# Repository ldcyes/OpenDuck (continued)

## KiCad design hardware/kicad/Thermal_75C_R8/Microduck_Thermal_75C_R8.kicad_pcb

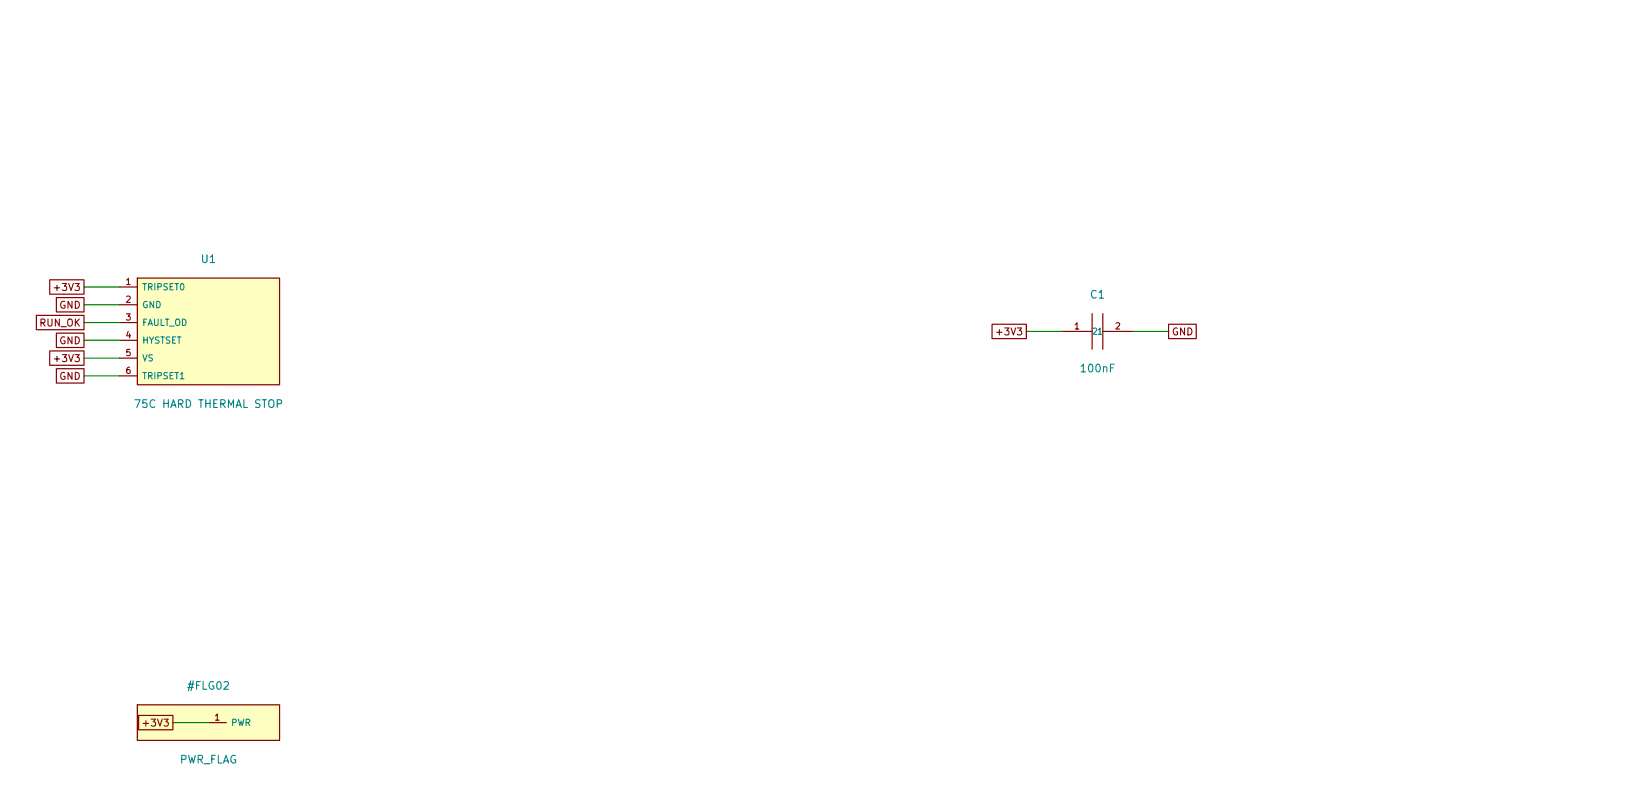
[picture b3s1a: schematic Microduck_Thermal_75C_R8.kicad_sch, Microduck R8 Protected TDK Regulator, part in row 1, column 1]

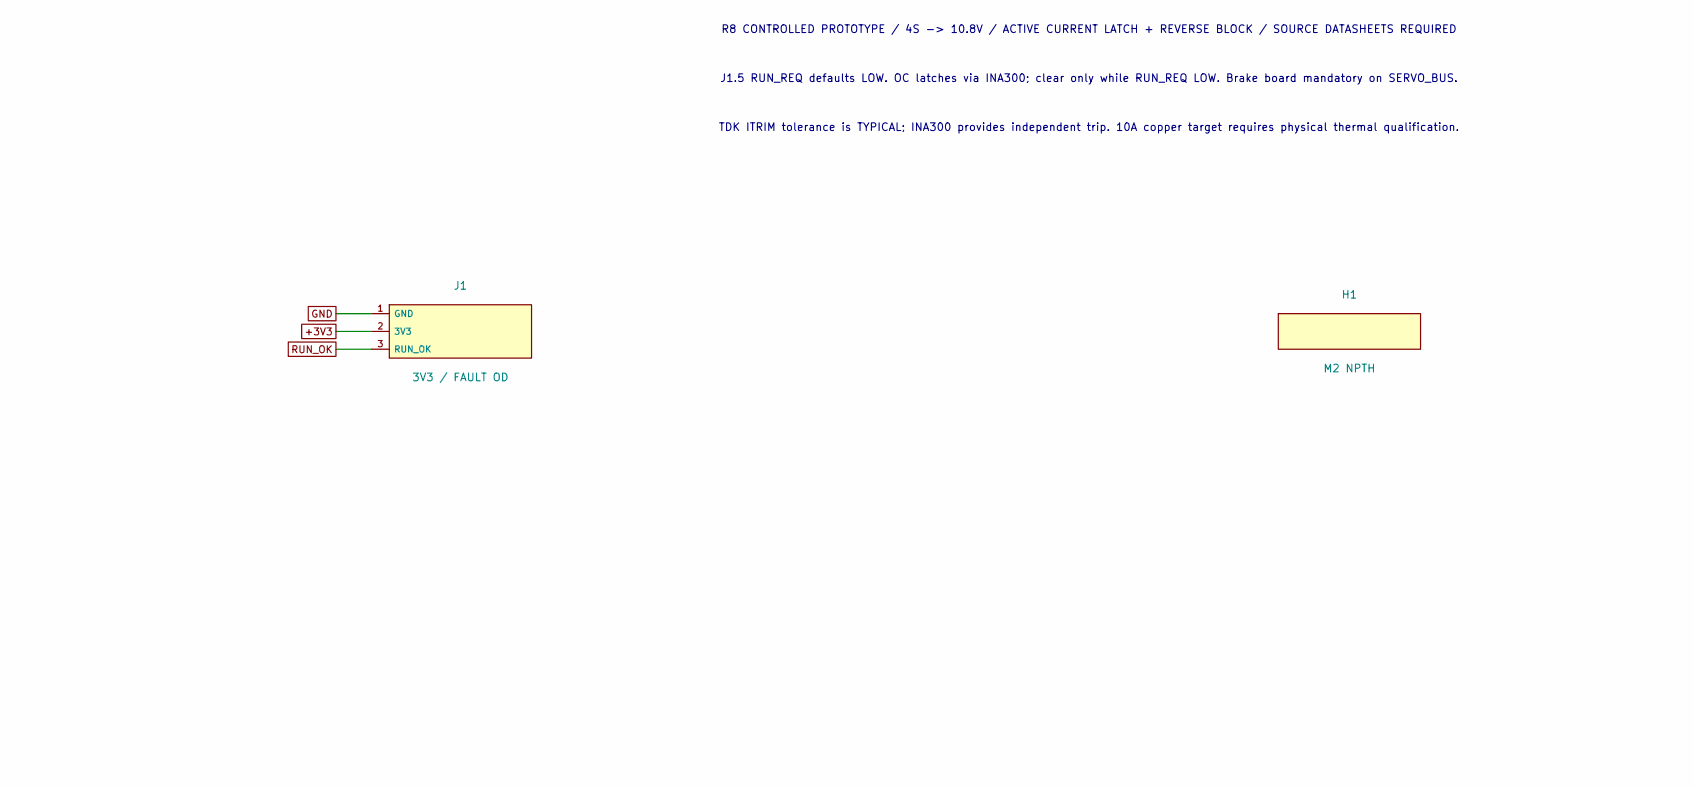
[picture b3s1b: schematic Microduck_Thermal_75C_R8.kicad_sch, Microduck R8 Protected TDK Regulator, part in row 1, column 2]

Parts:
C1: 100nF; C_0603_1608Metric; MPN GRM188R71H104KA93D
H1, H2: M2 NPTH; MountingHole_2.2mm_M2; MPN NO PART
J1: 3V3 / FAULT OD; JST_SH_SM03B-SRSS-TB_1x03-1MP_P1.00mm_Horizontal; MPN SM03B-SRSS-TB(LF)(SN)
U1: 75C HARD THERMAL STOP; SOT-563; MPN TMP302BDRLR

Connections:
+3V3: C1.1, J1.2 (3V3), U1.1 (TRIPSET0), U1.5 (VS)
GND: C1.2, J1.1 (GND), U1.2 (GND), U1.4 (HYSTSET), U1.6 (TRIPSET1)
RUN_OK: J1.3 (RUN_OK), U1.3 (FAULT_OD)

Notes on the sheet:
R8 CONTROLLED PROTOTYPE / 4S -> 10.8V / ACTIVE CURRENT LATCH + REVERSE BLOCK / SOURCE DATASHEETS REQUIRED
J1.5 RUN_REQ defaults LOW. OC latches via INA300; clear only while RUN_REQ LOW. Brake board mandatory on SERVO_BUS.
TDK ITRIM tolerance is TYPICAL; INA300 provides independent trip. 10A copper target requires physical thermal qualification.

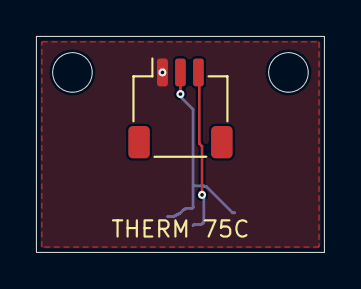
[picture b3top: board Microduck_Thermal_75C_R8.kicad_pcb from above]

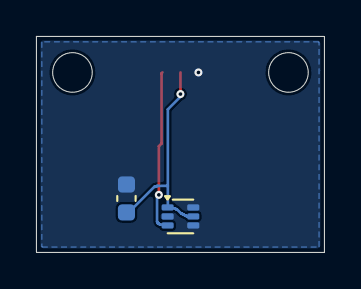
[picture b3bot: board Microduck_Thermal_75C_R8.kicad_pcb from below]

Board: 2 copper layers, 16.0 x 12.0 mm, 5 parts (2 on the bottom side), 3 nets.

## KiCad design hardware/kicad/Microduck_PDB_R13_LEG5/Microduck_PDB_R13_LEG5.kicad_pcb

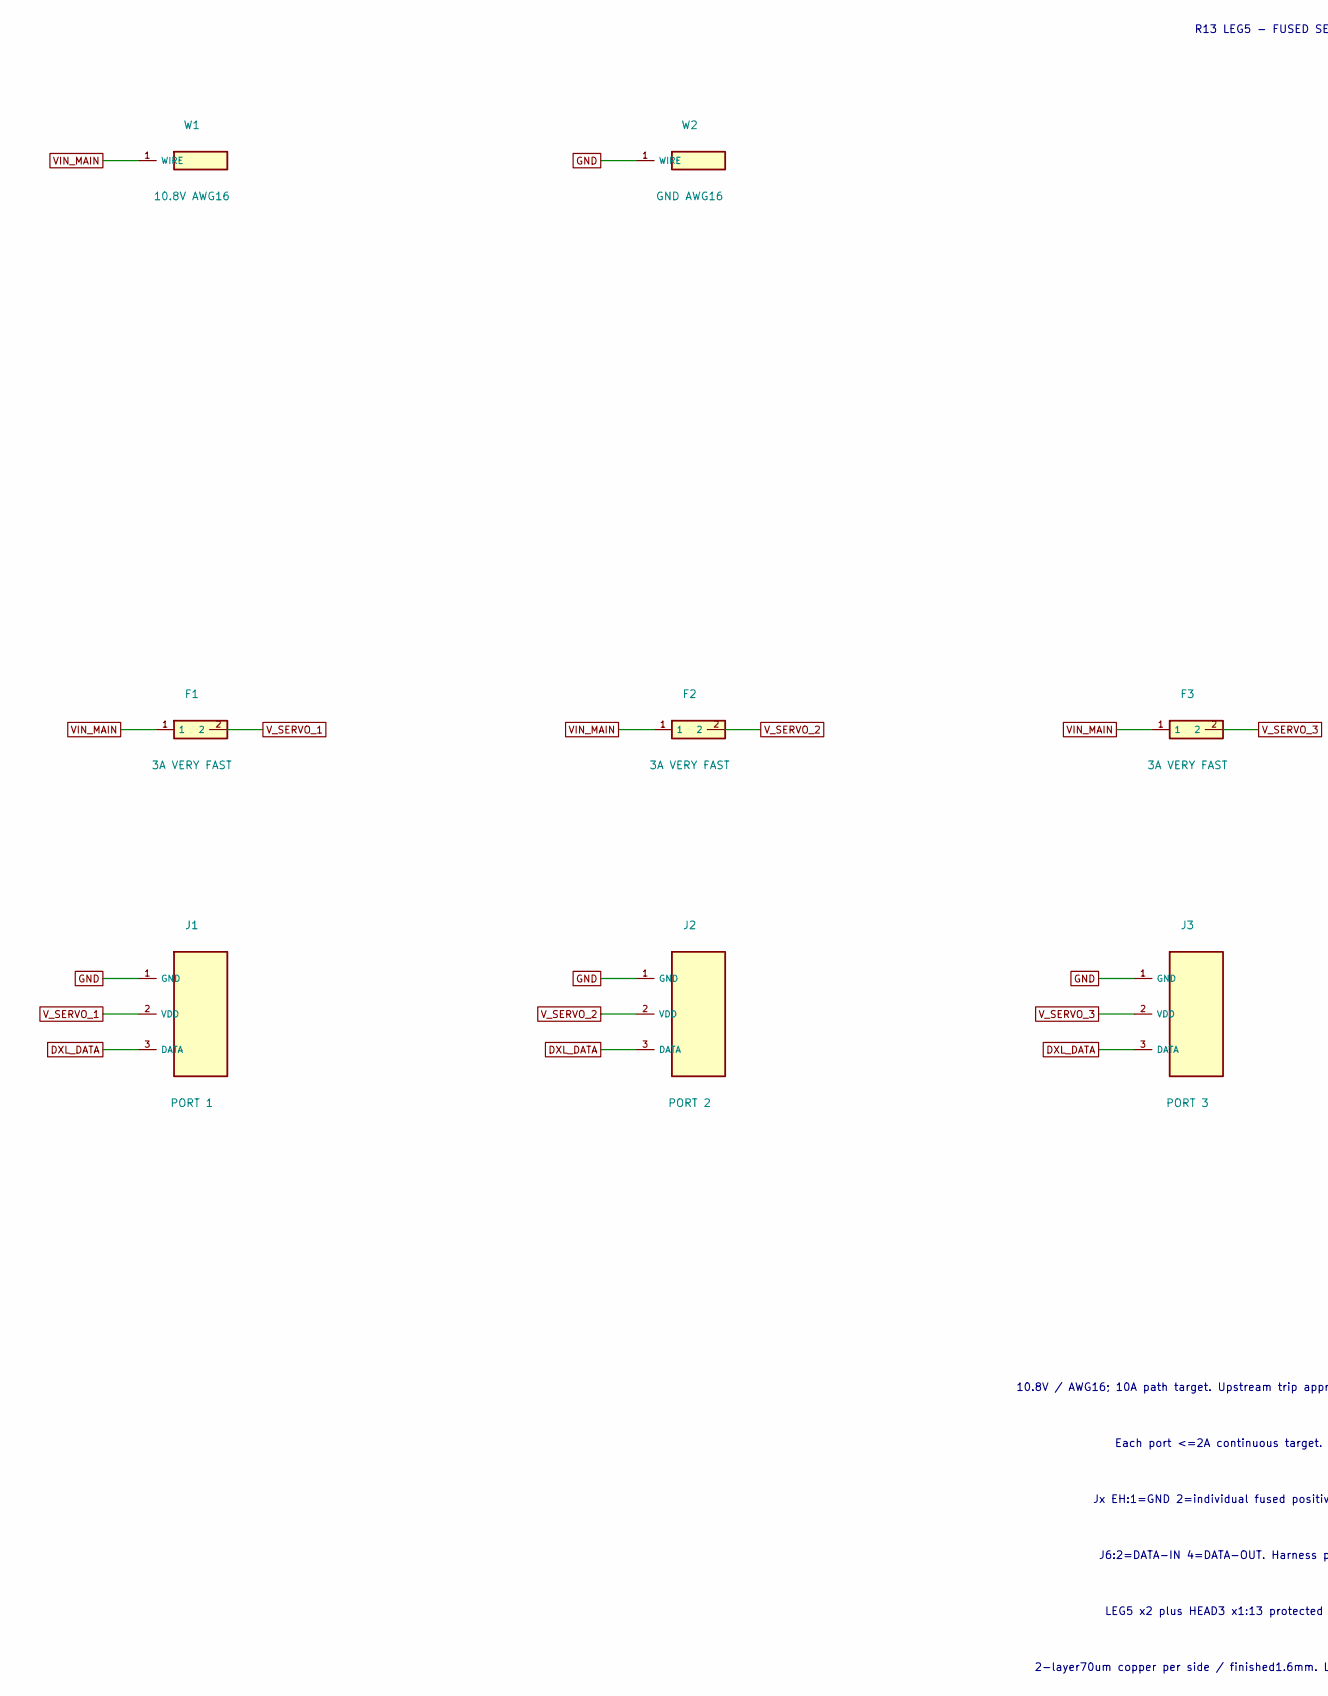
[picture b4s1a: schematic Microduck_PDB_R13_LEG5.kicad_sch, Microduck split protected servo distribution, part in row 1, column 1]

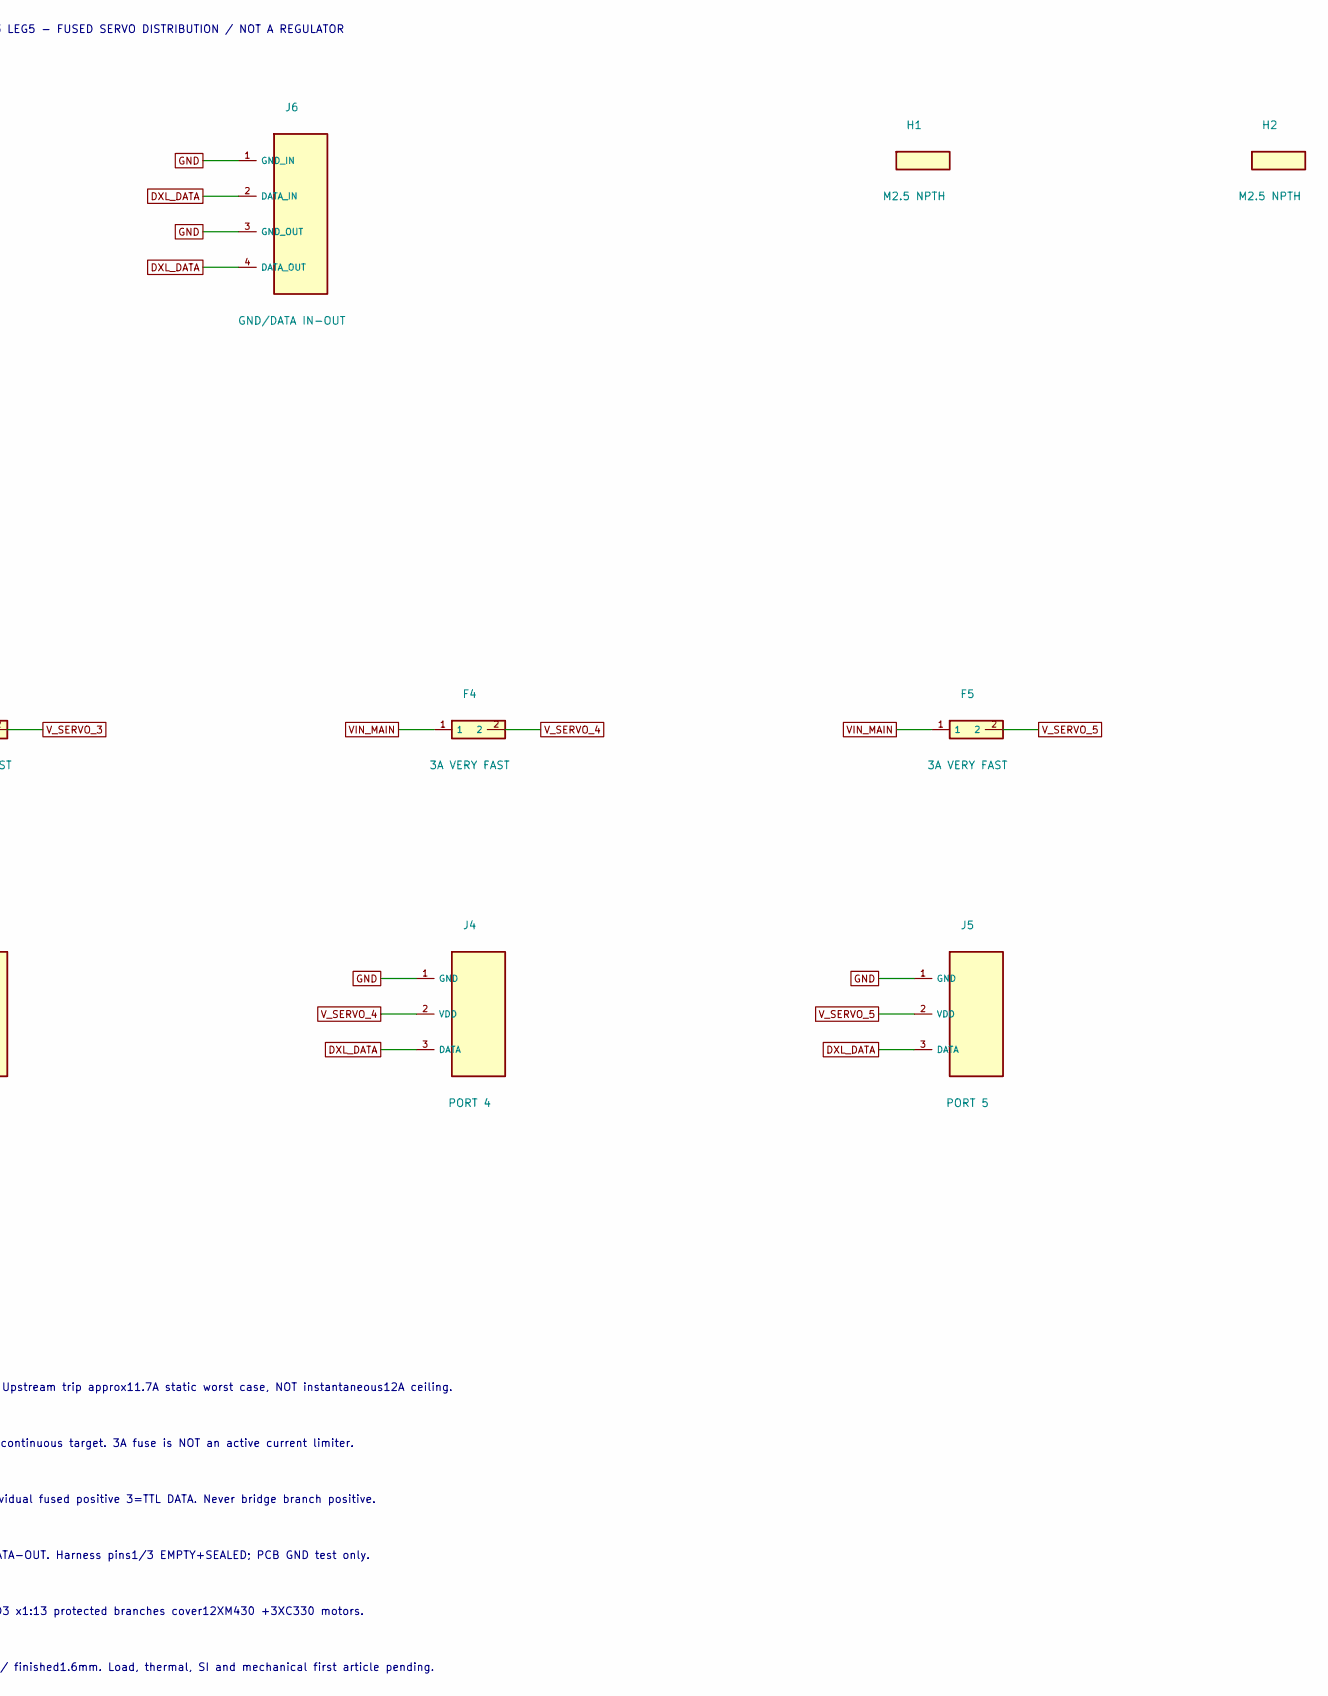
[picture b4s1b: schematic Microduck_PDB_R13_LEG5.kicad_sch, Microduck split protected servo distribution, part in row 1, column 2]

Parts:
F1, F2, F3, F4, F5: 3A VERY FAST; Fuse_Littelfuse_448; MPN 0448003.MR
H1, H2: M2.5 NPTH; MountingHole_2.7mm_M2.5; MPN NO PART
J1: PORT 1; JST_EH_S3B-EH_1x03_P2.50mm_Horizontal; MPN S3B-EH(LF)(SN)
J2: PORT 2; JST_EH_S3B-EH_1x03_P2.50mm_Horizontal; MPN S3B-EH(LF)(SN)
J3: PORT 3; JST_EH_S3B-EH_1x03_P2.50mm_Horizontal; MPN S3B-EH(LF)(SN)
J4: PORT 4; JST_EH_S3B-EH_1x03_P2.50mm_Horizontal; MPN S3B-EH(LF)(SN)
J5: PORT 5; JST_EH_S3B-EH_1x03_P2.50mm_Horizontal; MPN S3B-EH(LF)(SN)
J6: GND/DATA IN-OUT; JST_SH_SM04B-SRSS-TB_1x04-1MP_P1.00mm_Horizontal; MPN SM04B-SRSS-TB(LF)(SN)
W1: 10.8V AWG16; WirePad_2p4mm_6mm; MPN WIRE55A0111-16-2
W2: GND AWG16; WirePad_2p4mm_6mm; MPN WIRE55A0111-16-0

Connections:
DXL_DATA: J1.3 (DATA), J2.3 (DATA), J3.3 (DATA), J4.3 (DATA), J5.3 (DATA), J6.2 (DATA_IN), J6.4 (DATA_OUT)
GND: J1.1 (GND), J2.1 (GND), J3.1 (GND), J4.1 (GND), J5.1 (GND), J6.1 (GND_IN), J6.3 (GND_OUT), W2.1
VIN_MAIN: F1.1, F2.1, F3.1, F4.1, F5.1, W1.1
V_SERVO_1: F1.2, J1.2 (VDD)
V_SERVO_2: F2.2, J2.2 (VDD)
V_SERVO_3: F3.2, J3.2 (VDD)
V_SERVO_4: F4.2, J4.2 (VDD)
V_SERVO_5: F5.2, J5.2 (VDD)

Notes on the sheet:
R13 LEG5 - FUSED SERVO DISTRIBUTION / NOT A REGULATOR
10.8V / AWG16; 10A path target. Upstream trip approx11.7A static worst case, NOT instantaneous12A ceiling.
Each port <=2A continuous target. 3A fuse is NOT an active current limiter.
Jx EH:1=GND 2=individual fused positive 3=TTL DATA. Never bridge branch positive.
J6:2=DATA-IN 4=DATA-OUT. Harness pins1/3 EMPTY+SEALED; PCB GND test only.
LEG5 x2 plus HEAD3 x1:13 protected branches cover12XM430 +3XC330 motors.
2-layer70um copper per side / finished1.6mm. Load, thermal, SI and mechanical first article pending.

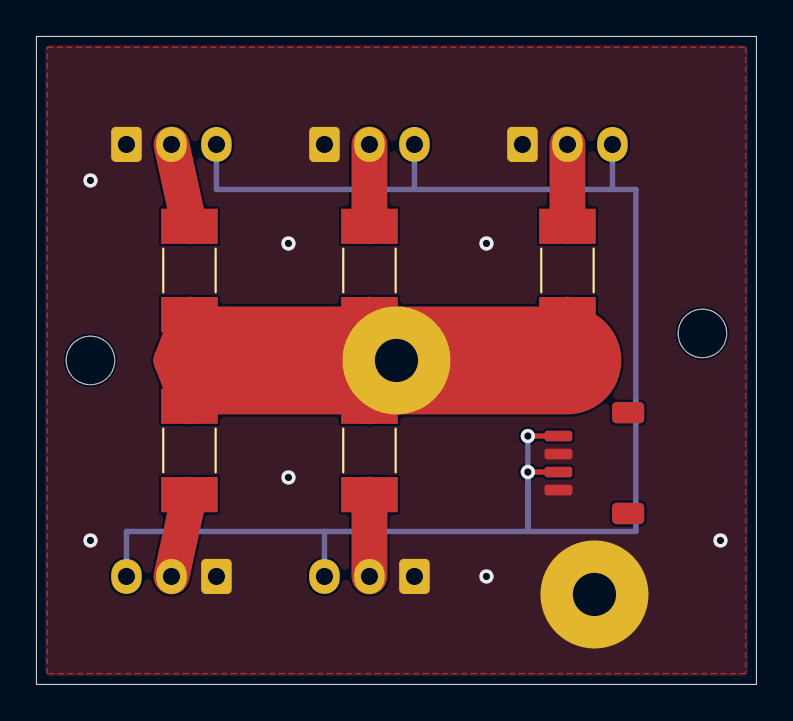
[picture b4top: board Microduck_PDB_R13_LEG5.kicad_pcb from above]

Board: 2 copper layers, 40.0 x 36.0 mm, 15 parts (0 on the bottom side), 8 nets.

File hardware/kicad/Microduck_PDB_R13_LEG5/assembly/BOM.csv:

Reference,Quantity,MPN,Value,Footprint,Mounting,Scope,Datasheet
J1,1,S3B-EH(LF)(SN),PORT 1,Connector_JST:JST_EH_S3B-EH_1x03_P2.50mm_Horizontal,THT,one PCB; matching housings/terminals in harness BOM,https://www.jst-mfg.com/product/pdf/eng/eEH.pdf
F1,1,0448003.MR,3A VERY FAST,Microduck_PDB_R13:Fuse_Littelfuse_448,SMT,one PCB; matching housings/terminals in harness BOM,https://www.littelfuse.com/assetdocs/littelfuse_fuse_448_dat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
J2,1,S3B-EH(LF)(SN),PORT 2,Connector_JST:JST_EH_S3B-EH_1x03_P2.50mm_Horizontal,THT,one PCB; matching housings/terminals in harness BOM,https://www.jst-mfg.com/product/pdf/eng/eEH.pdf
F2,1,0448003.MR,3A VERY FAST,Microduck_PDB_R13:Fuse_Littelfuse_448,SMT,one PCB; matching housings/terminals in harness BOM,https://www.littelfuse.com/assetdocs/littelfuse_fuse_448_dat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
J3,1,S3B-EH(LF)(SN),PORT 3,Connector_JST:JST_EH_S3B-EH_1x03_P2.50mm_Horizontal,THT,one PCB; matching housings/terminals in harness BOM,https://www.jst-mfg.com/product/pdf/eng/eEH.pdf
F3,1,0448003.MR,3A VERY FAST,Microduck_PDB_R13:Fuse_Littelfuse_448,SMT,one PCB; matching housings/terminals in harness BOM,https://www.littelfuse.com/assetdocs/littelfuse_fuse_448_dat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
J4,1,S3B-EH(LF)(SN),PORT 4,Connector_JST:JST_EH_S3B-EH_1x03_P2.50mm_Horizontal,THT,one PCB; matching housings/terminals in harness BOM,https://www.jst-mfg.com/product/pdf/eng/eEH.pdf
F4,1,0448003.MR,3A VERY FAST,Microduck_PDB_R13:Fuse_Littelfuse_448,SMT,one PCB; matching housings/terminals in harness BOM,https://www.littelfuse.com/assetdocs/littelfuse_fuse_448_dat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
J5,1,S3B-EH(LF)(SN),PORT 5,Connector_JST:JST_EH_S3B-EH_1x03_P2.50mm_Horizontal,THT,one PCB; matching housings/terminals in harness BOM,https://www.jst-mfg.com/product/pdf/eng/eEH.pdf
F5,1,0448003.MR,3A VERY FAST,Microduck_PDB_R13:Fuse_Littelfuse_448,SMT,one PCB; matching housings/terminals in harness BOM,https://www.littelfuse.com/assetdocs/littelfuse_fuse_448_dat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
J6,1,SM04B-SRSS-TB(LF)(SN),GND/DATA IN-OUT,Connector_JST:JST_SH_SM04B-SRSS-TB_1x04-1MP_P1.00mm_Horizontal,SMT,one PCB; matching housings/terminals in harness BOM,https://www.jst-mfg.com/product/pdf/eng/eSH.pdf

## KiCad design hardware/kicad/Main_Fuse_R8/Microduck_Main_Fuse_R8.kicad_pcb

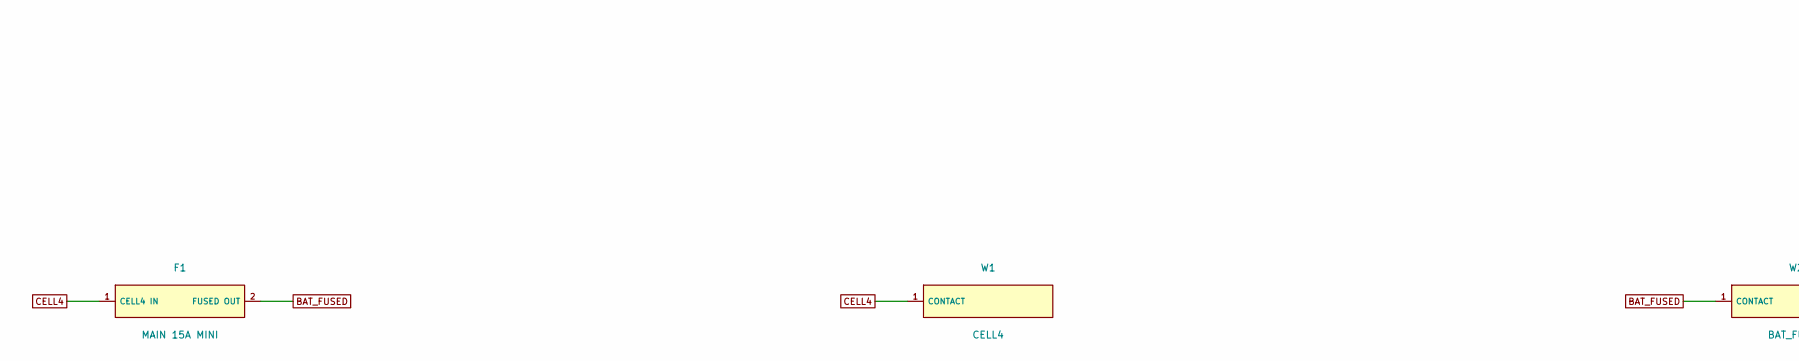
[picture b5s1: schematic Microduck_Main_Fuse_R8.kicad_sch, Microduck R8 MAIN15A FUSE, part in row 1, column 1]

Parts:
F1: MAIN 15A MINI; Keystone_3549_2_Horizontal; MPN 3549-2 + 0297015.WXNV
H1, H2: M2 NPTH; MountingHole_2.2mm_M2; MPN NO PART
W1: CELL4; Wire_SMD5; MPN AWG16 solder with independent clamp
W2: BAT_FUSED; Wire_SMD5; MPN AWG16 solder with independent clamp

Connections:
BAT_FUSED: F1.2 (FUSED OUT), W2.1
CELL4: F1.1 (CELL4 IN), W1.1

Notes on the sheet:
CELL4 positive -> W1 -> 0297015.WXNV 15A32VDC in Keystone3549-2 -> W2 BAT_FUSED
Install close to battery positive, source wire target<=50mm; isolated fixed harness; not Entry logic2A fuse.
Holder20A is contact rating; blade15A is time-current fuse, not instantaneous15A limit. Only replace with battery disconnected.

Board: 2 copper layers, 5 parts (2 on the bottom side), 2 nets, no tracks yet.

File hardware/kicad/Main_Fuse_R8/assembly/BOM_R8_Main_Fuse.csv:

reference,MPN,qty,note
F1.H,Keystone3549-2,1,Horizontal MINI holder20A
F1.E,Littelfuse0297015.WXNV,1,15A32VDC fuse; blue
W1/W2,AWG16 insulated copper solder tails,2,Independent clamp;maxbackheight3mm
H1/H2,M2 insulated mounting hardware,2,Hardware from integration CAD

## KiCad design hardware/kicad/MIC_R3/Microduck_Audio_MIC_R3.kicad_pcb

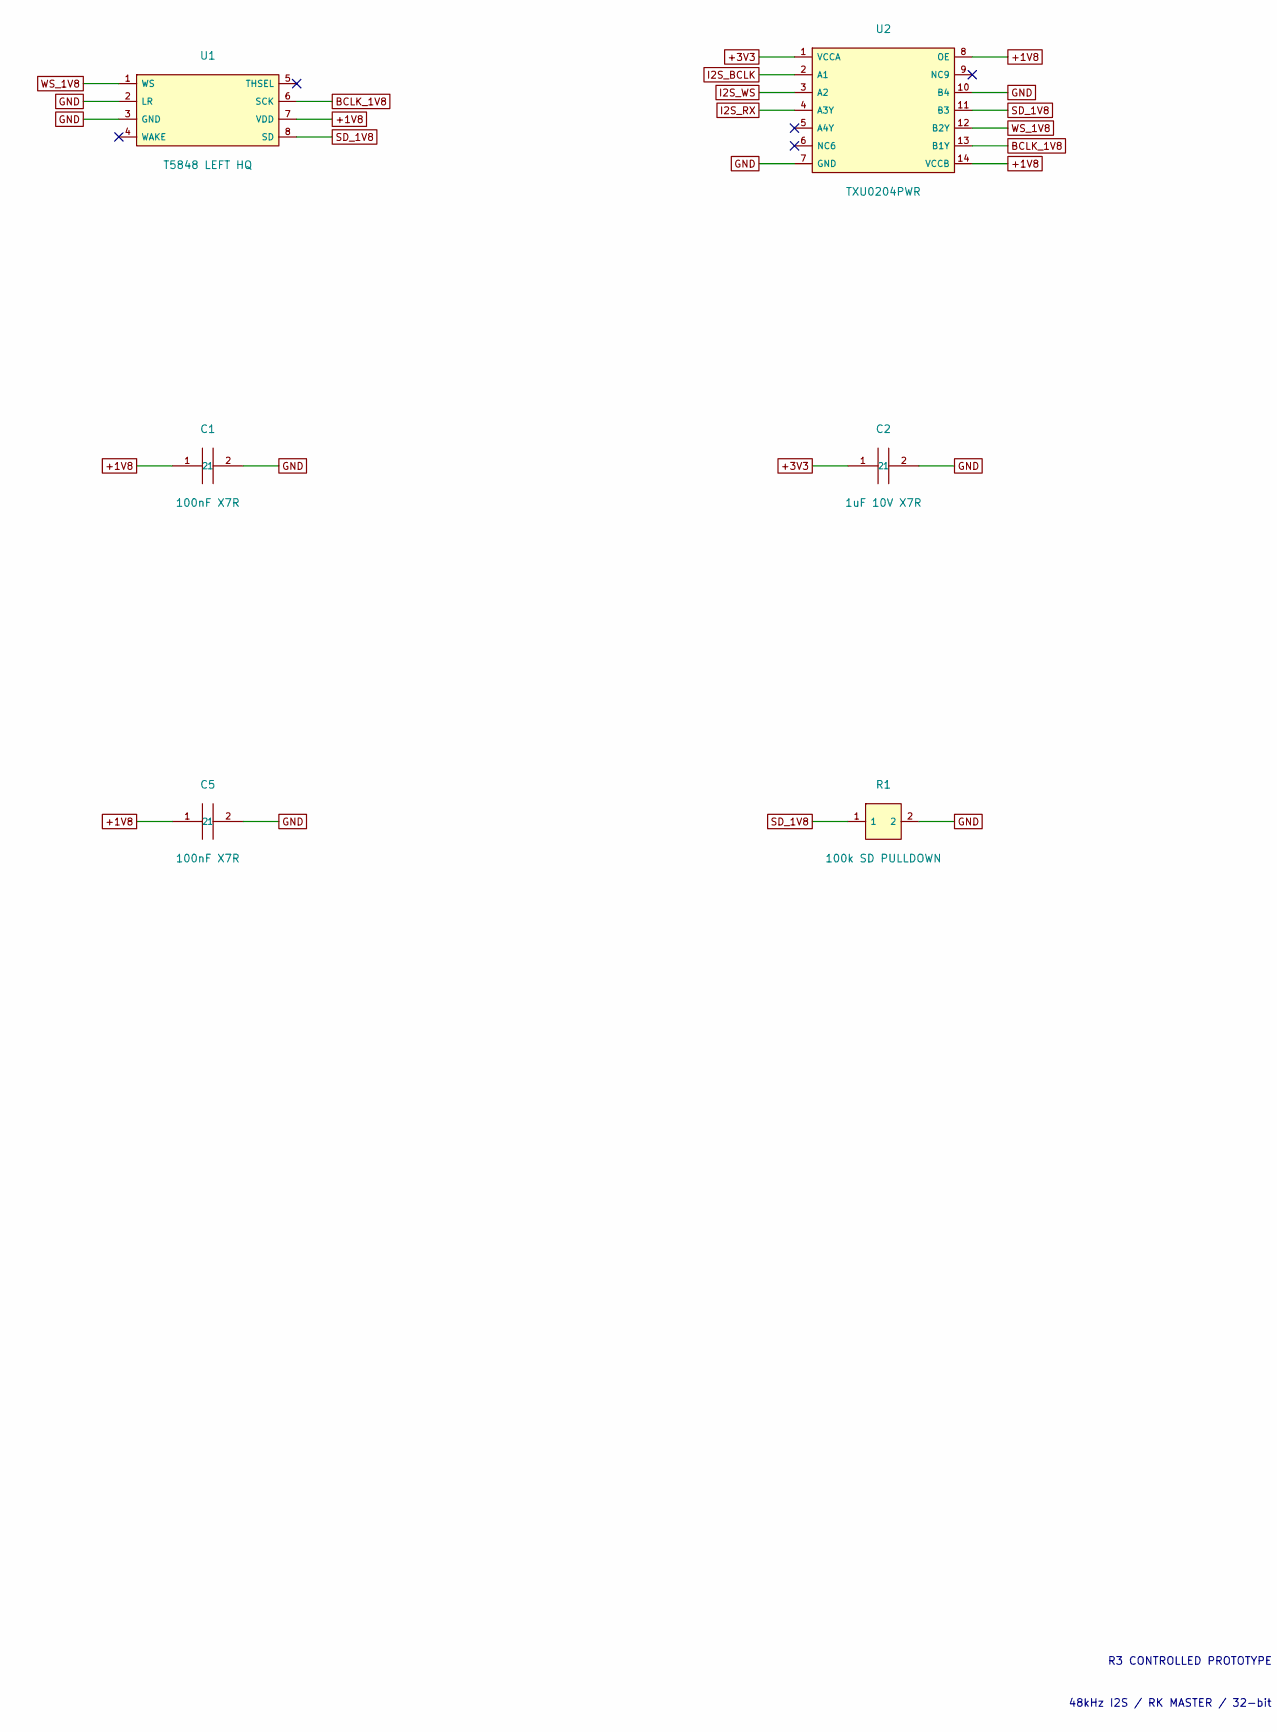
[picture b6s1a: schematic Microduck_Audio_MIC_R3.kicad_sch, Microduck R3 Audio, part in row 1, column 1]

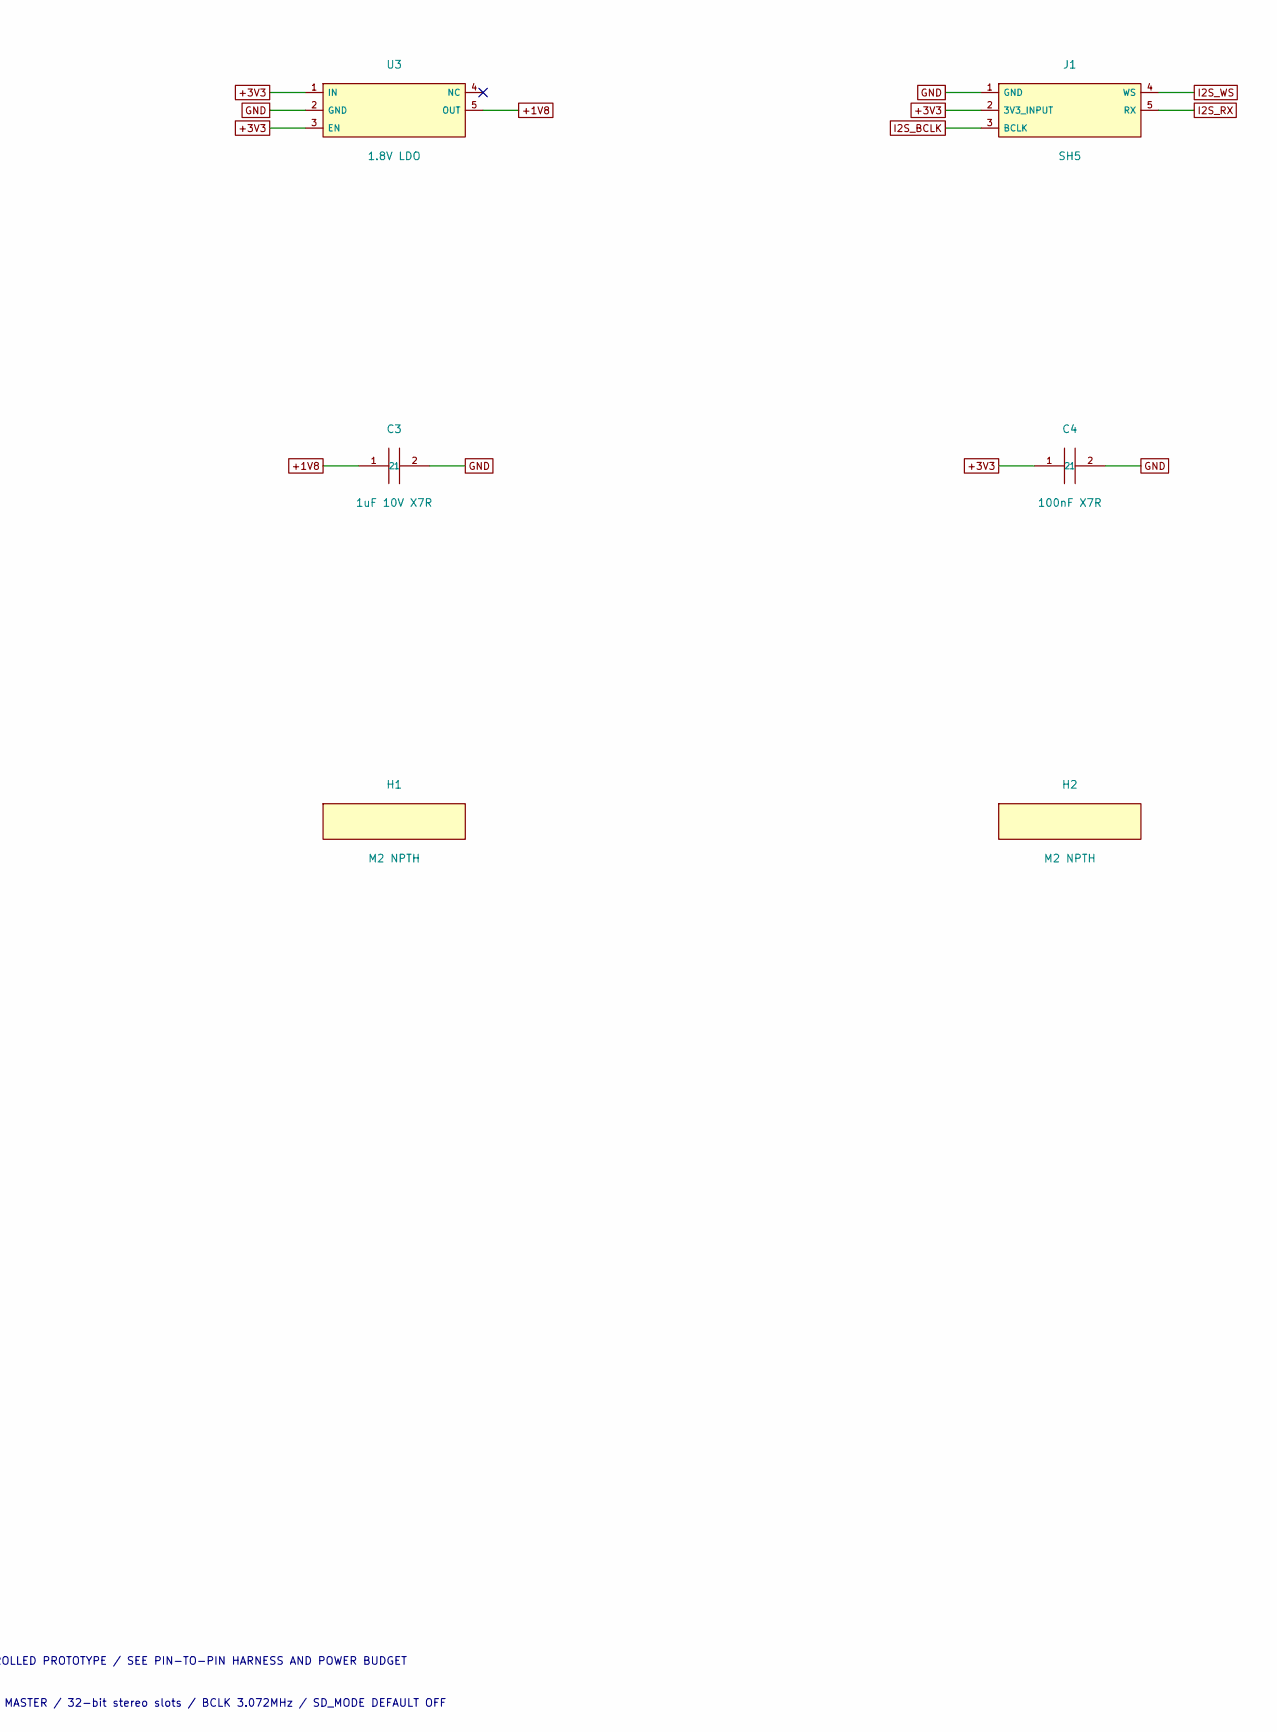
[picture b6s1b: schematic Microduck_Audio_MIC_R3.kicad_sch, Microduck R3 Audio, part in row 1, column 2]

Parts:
C1, C4, C5: 100nF X7R; C_0603_1608Metric; MPN GRM188R71C104KA01D
C2, C3: 1uF 10V X7R; C_0603_1608Metric; MPN GRM188R71A105KA61D
H1, H2: M2 NPTH; MountingHole_2.2mm_M2; MPN NO PART
J1: SH5; JST_SH_SM05B-SRSS-TB_1x05-1MP_P1.00mm_Horizontal; MPN SM05B-SRSS-TB(LF)(SN)
R1: 100k SD PULLDOWN; R_0603_1608Metric; MPN RC0603FR-07100KL
U1: T5848 LEFT HQ; T5848_LGA8_BottomPort; MPN MMICT5848-00-012
U2: TXU0204PWR; TSSOP-14_4.4x5mm_P0.65mm; MPN TXU0204PWR
U3: 1.8V LDO; SOT-23-5; MPN TLV75518PDBVR

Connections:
+1V8: C1.1, C3.1, C5.1, U1.7 (VDD), U2.8 (OE), U2.14 (VCCB), U3.5 (OUT)
+3V3: C2.1, C4.1, J1.2 (3V3_INPUT), U2.1 (VCCA), U3.1 (IN), U3.3 (EN)
BCLK_1V8: U1.6 (SCK), U2.13 (B1Y)
GND: C1.2, C2.2, C3.2, C4.2, C5.2, J1.1 (GND), R1.2, U1.2 (LR), U1.3 (GND), U2.7 (GND), U2.10 (B4), U3.2 (GND)
I2S_BCLK: J1.3 (BCLK), U2.2 (A1)
I2S_RX: J1.5 (RX), U2.4 (A3Y)
I2S_WS: J1.4 (WS), U2.3 (A2)
SD_1V8: R1.1, U1.8 (SD), U2.11 (B3)
WS_1V8: U1.1 (WS), U2.12 (B2Y)

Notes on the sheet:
R3 CONTROLLED PROTOTYPE / SEE PIN-TO-PIN HARNESS AND POWER BUDGET
48kHz I2S / RK MASTER / 32-bit stereo slots / BCLK 3.072MHz / SD_MODE DEFAULT OFF

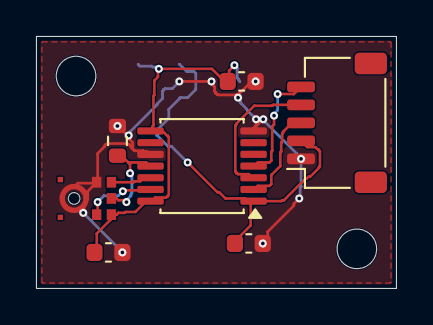
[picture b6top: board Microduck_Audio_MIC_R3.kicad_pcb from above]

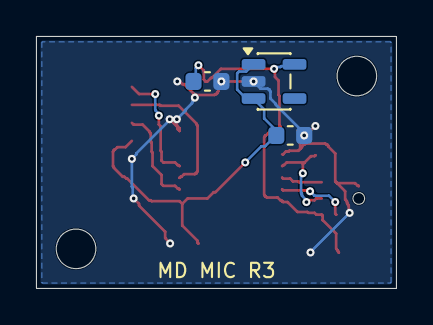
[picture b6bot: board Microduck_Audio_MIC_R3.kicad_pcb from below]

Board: 2 copper layers, 20.0 x 14.0 mm, 12 parts (3 on the bottom side), 9 nets.

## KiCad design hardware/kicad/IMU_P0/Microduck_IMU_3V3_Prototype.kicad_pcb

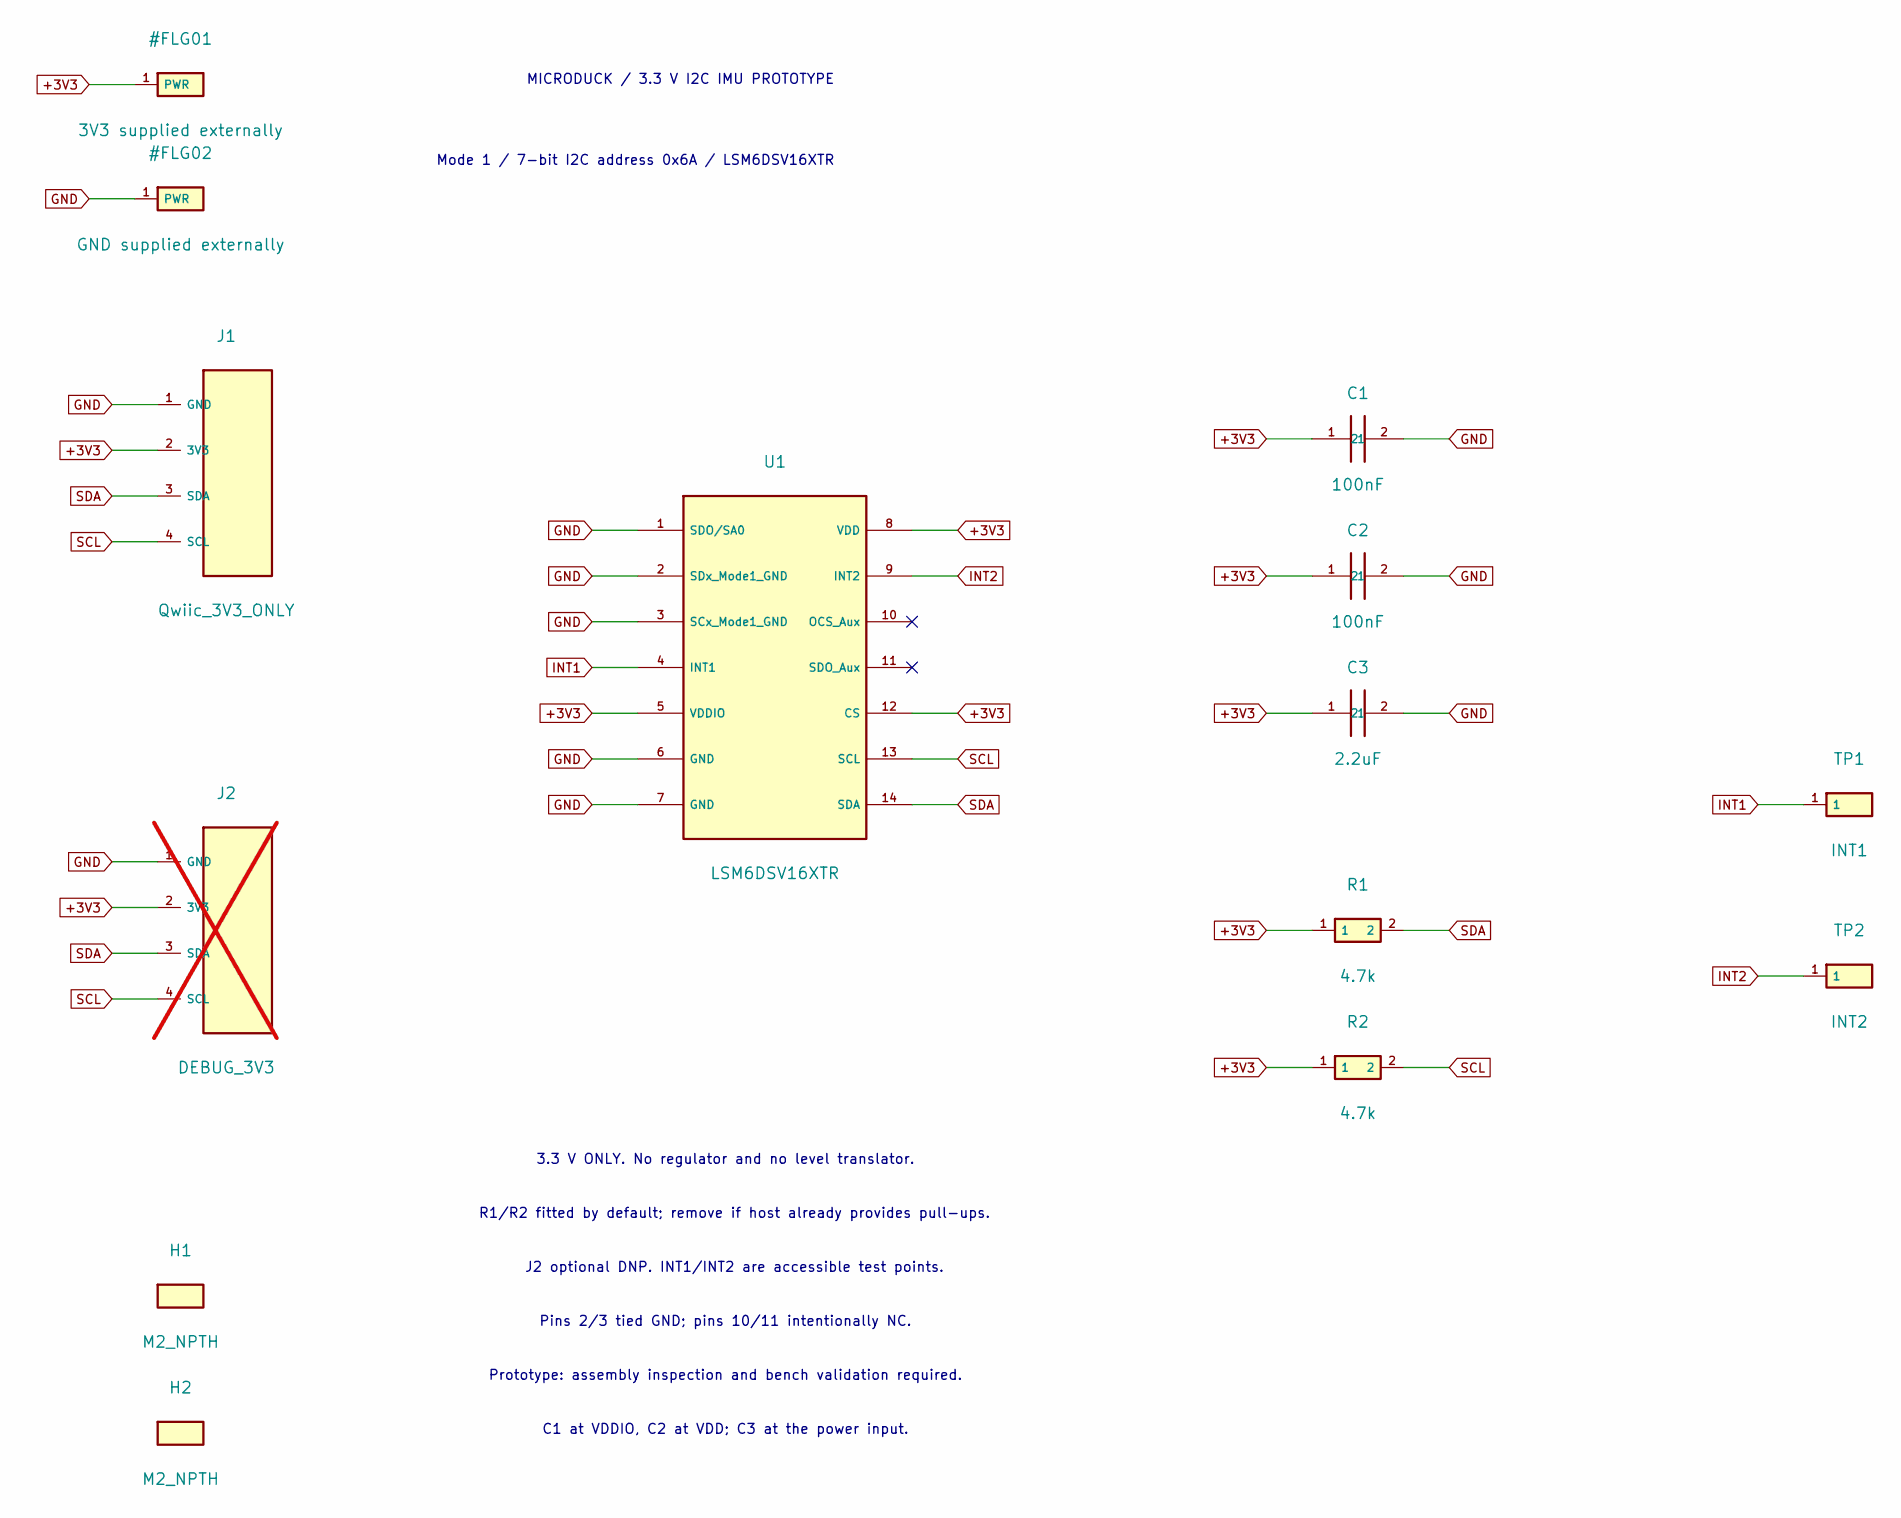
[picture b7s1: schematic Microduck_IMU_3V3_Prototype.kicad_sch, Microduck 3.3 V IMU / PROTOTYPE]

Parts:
C1, C2: 100nF; C_0603_1608Metric; MPN CC0603KRX7R9BB104
C3: 2.2uF; C_0603_1608Metric; MPN GRM188R71A225KE15D
H1, H2: M2_NPTH; MountingHole_2.2mm_M2; MPN 2.2 mm NPTH
J1: Qwiic_3V3_ONLY; JST_SH_SM04B-SRSS-TB_1x04-1MP_P1.00mm_Horizontal; MPN SM04B-SRSS-TB(LF)(SN)
J2: DEBUG_3V3; PinHeader_1x04_P2.54mm_Vertical; MPN 2.54mm 1x04 TH header; optional; not fitted
R1, R2: 4.7k; R_0603_1608Metric; MPN RC0603FR-074K7L
TP1: INT1; TestPoint_Pad_D1.0mm; MPN PCB test point 1 mm
TP2: INT2; TestPoint_Pad_D1.0mm; MPN PCB test point 1 mm
U1: LSM6DSV16XTR; LSM6DSV16X_LGA14; MPN LSM6DSV16XTR

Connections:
+3V3: C1.1, C2.1, C3.1, J1.2 (3V3), J2.2 (3V3), R1.1, R2.1, U1.5 (VDDIO), U1.8 (VDD), U1.12 (CS)
GND: C1.2, C2.2, C3.2, J1.1 (GND), J2.1 (GND), U1.1 (SDO/SA0), U1.2 (SDx_Mode1_GND), U1.3 (SCx_Mode1_GND), U1.6 (GND), U1.7 (GND)
INT1: TP1.1, U1.4 (INT1)
INT2: TP2.1, U1.9 (INT2)
SCL: J1.4 (SCL), J2.4 (SCL), R2.2, U1.13 (SCL)
SDA: J1.3 (SDA), J2.3 (SDA), R1.2, U1.14 (SDA)

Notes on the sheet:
MICRODUCK / 3.3 V I2C IMU PROTOTYPE
Mode 1 / 7-bit I2C address 0x6A / LSM6DSV16XTR
3.3 V ONLY. No regulator and no level translator.
R1/R2 fitted by default; remove if host already provides pull-ups.
J2 optional DNP. INT1/INT2 are accessible test points.
Pins 2/3 tied GND; pins 10/11 intentionally NC.
Prototype: assembly inspection and bench validation required.
C1 at VDDIO, C2 at VDD; C3 at the power input.

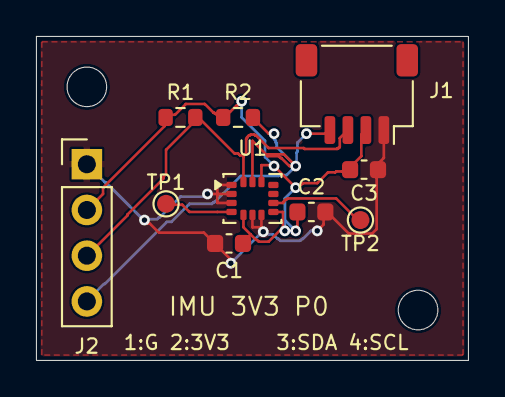
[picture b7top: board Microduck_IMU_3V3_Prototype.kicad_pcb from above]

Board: 2 copper layers, 24.0 x 18.0 mm, 12 parts (0 on the bottom side), 6 nets.
